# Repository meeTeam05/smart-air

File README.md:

# smart-air

> `smart-air` is an ESP32-S3 indoor air quality monitor and smart home controller. It combines ESP-IDF firmware, a Fastify + EMQX + TimescaleDB server stack, and a Flutter mobile app to solve device onboarding, telemetry ingestion, remote control, and live state sync in one system.

## Introduction

Devices provision over BLE, publish telemetry/shadow over MQTT, and serve the app through a Cloudflare-fronted Fastify API. See **Features** below for the full breakdown. See the **Hardware** section for the board, sensors, and enclosure.

## Features

- **Firmware** (ESP-IDF v5.4.2): BLE provisioning, Wi-Fi, MQTT over TLS/WSS, HTTPS OTA with rollback/validation, SHT3x (temperature/humidity), GM702B (CO) and GM102B (NO₂) gas sensors, DS3231 RTC with SNTP sync, LVGL on ILI9225 display, 3 relay channels (Fan/Lamp/Filter) with NVS persistence, WS2812 status LED, buzzer, and factory-reset button.
- **Server**: Fastify API with PostgreSQL/TimescaleDB, Redis, and EMQX in Docker Compose; Nginx + Cloudflare Tunnel for public ingress; per-device MQTT credentials provisioned through the API; OTA artifact hosting.
- **Realtime**: Live device status, shadow, telemetry, OTA progress, and command updates over Server-Sent Events; REST remains canonical for snapshots, history, replay, and command authorization.
- **App** (Flutter + Riverpod): JWT auth with refresh-token rotation in secure storage, 5-step BLE provisioning, multi-home/room management with member invites, device dashboard with relay and device-mode controls, real-time sparkline charts, command history, sensor calibration wizard, OTA screen, in-app notifications, and adaptive light/dark theme.

## Hardware

### Schematic

### PCB Layout

### 3D Model

### Assembly

## Firmware

### Config and build

### Runtime

## App

### Demo

## Contributing

- For structural work, also read `docs/ARCHITECTURE.md`, `docs/MQTT_PROTOCOL.md`, and `docs/API_REFERENCE.md`.
- Keep changes narrow, update matching docs when contracts change, and run the narrowest verification for the area you touched.

## License

MIT. See [LICENSE.md](LICENSE.md).

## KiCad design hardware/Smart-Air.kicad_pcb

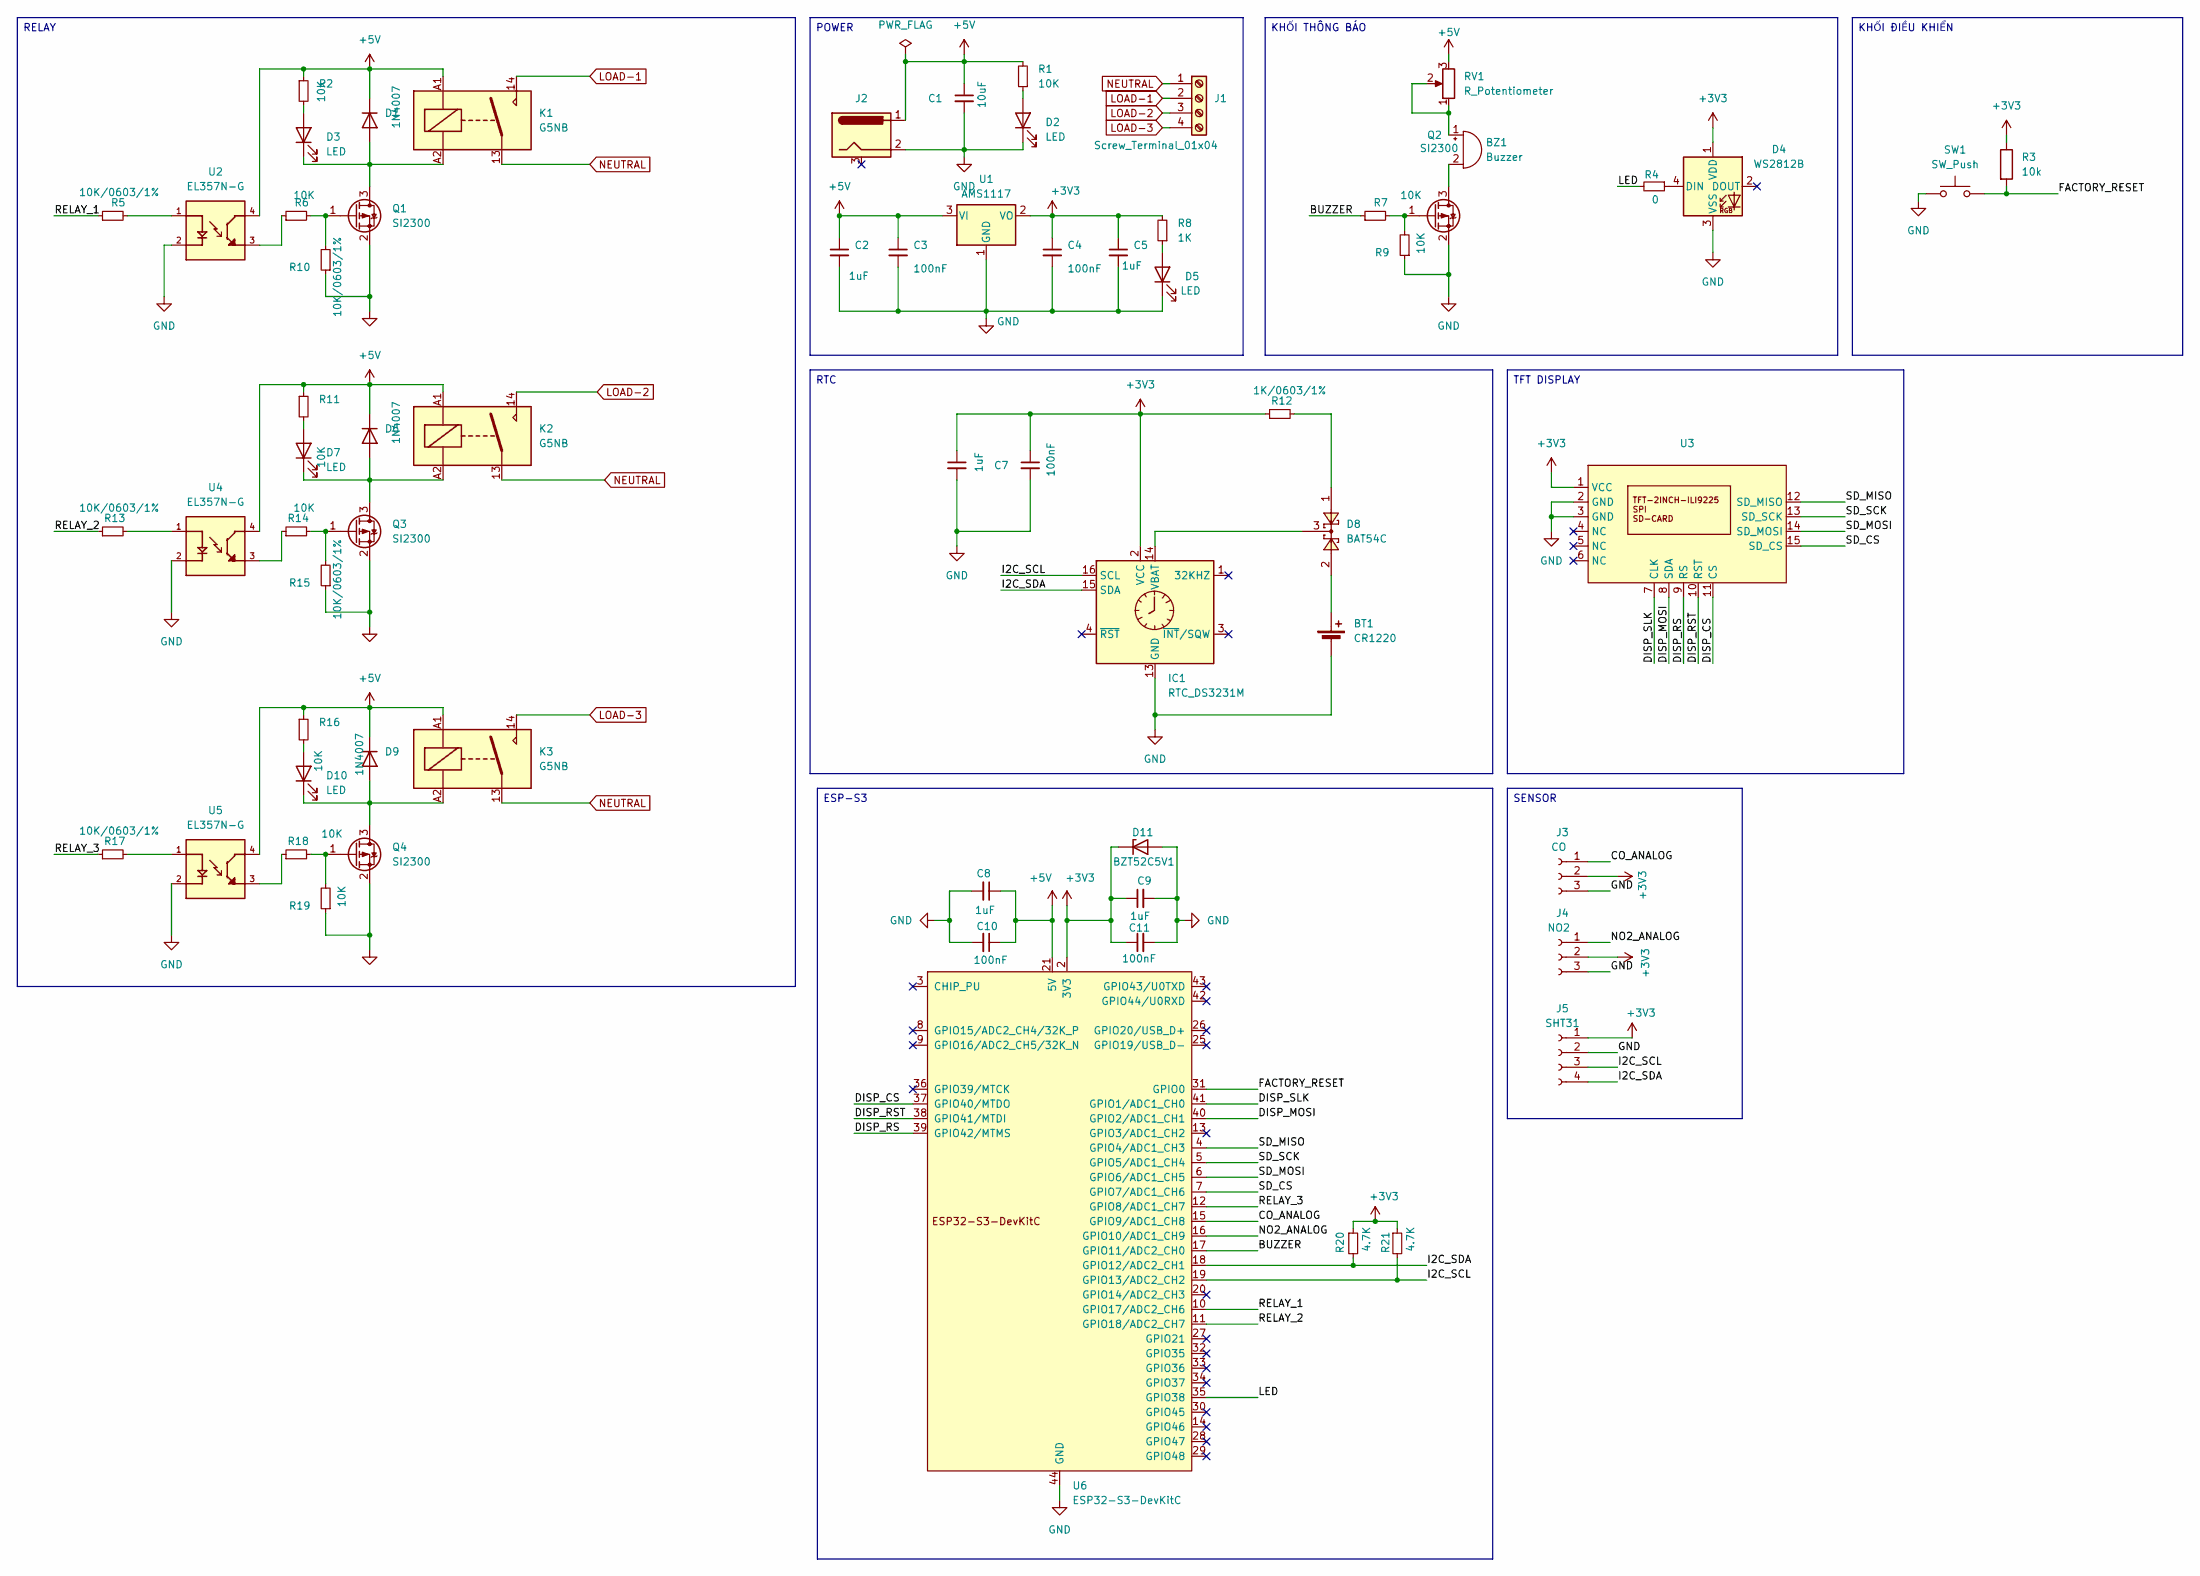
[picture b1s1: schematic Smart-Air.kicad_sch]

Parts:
BT1: CR1220; BatteryHolder-SMD-CR1220
BZ1: Buzzer; Buzzer-THT-12x9.5_RM7.6
C1: 10uF; C_0603
C2, C5, C6, C8, C9: 1uF; C_0603
C3, C4, C7, C10, C11: 100nF; C_0603
D1, D6, D9: 1N4007; D_SOD-123F
D2, D3, D5, D7, D10: LED; LED_0603_1608Metric
D4: WS2812B; LED_WS2812B_PLCC4_5.0x5.0mm_P3.2mm
D8: BAT54C; SOT23-3
D11: BZT52C5V1; D_SOD-123F
IC1: RTC_DS3231M; SOIC-16W_7.5x10.3mm_P1.27mm
J1: Screw_Terminal_01x04; HB9500-4P
J2: Conn_Jack-DC; BarrelJackDC-Horz-THT-5mm
J3: CO; PinSocket_1x03_P2.54mm_Vertical
J4: NO2; PinSocket_1x03_P2.54mm_Vertical
J5: SHT31; PinSocket_1x04_P2.54mm_Vertical
K1, K2, K3: G5NB; Relay_SPST_Omron_G5NB
Q1, Q2, Q3, Q4: SI2300; SOT-23
R1, R2, R6, R7, R9, R11, R14, R16, R18, R19: 10K; R_0603
R3: 10k; R_0603
R4: 0; R_0603
R5, R10, R13, R15, R17: 10K/0603/1%; R_0603
R8: 1K; R_0603
R12: 1K/0603/1%; R_0603
R20, R21: 4.7K; R_0603
RV1: R_Potentiometer; Potentiometer_Bourns_3266Y_Vertical
SW1: SW_Push; SW_PUSH_6mm
U1: AMS1117; SOT233
U2, U4, U5: EL357N-G; OPTO_EL357N-G; PARTREV 6
U3: TFT-ILI9225
U6: ESP32-S3-DevKitC

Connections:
+3V3: C4.1, C5.1, C6.1, C7.1, C9.1, C11.1, D4.1 (VDD), D11.1 (K), IC1.2 (VCC), J3.2, J4.2, J5.1, R3.1, R8.2, R12.1, R20.1, R21.1, U1.2 (VO), U3.1 (VCC), U6.1 (3V3), U6.2 (3V3)
+5V: C1.1, C2.1, C3.1, C8.1, C10.1, D1.1 (K), D6.1 (K), D9.1 (K), J2.1, K1.A1, K2.A1, K3.A1, R1.2, R2.1, R11.1, R16.1, RV1.3, U1.3 (VI), U2.4, U4.4, U5.4, U6.21 (5V)
/BUZZER: R7.1, U6.17 (GPIO11/ADC2_CH0)
/CO_ANALOG: J3.1, U6.15 (GPIO9/ADC1_CH8)
/DISP_CS: U3.11 (CS), U6.37 (GPIO40/MTDO)
/DISP_MOSI: U3.8 (SDA), U6.40 (GPIO2/ADC1_CH1)
/DISP_RS: U3.9 (RS), U6.39 (GPIO42/MTMS)
/DISP_RST: U3.10 (RST), U6.38 (GPIO41/MTDI)
/DISP_SLK: U3.7 (CLK), U6.41 (GPIO1/ADC1_CH0)
/FACTORY_RESET: R3.2, SW1.2, U6.31 (GPIO0)
/I2C_SCL: IC1.16 (SCL), J5.3, R21.2, U6.19 (GPIO13/ADC2_CH2)
/I2C_SDA: IC1.15 (SDA), J5.4, R20.2, U6.18 (GPIO12/ADC2_CH1)
/LED: R4.2, U6.35 (GPIO38)
/NO2_ANALOG: J4.1, U6.16 (GPIO10/ADC1_CH9)
/RELAY_1: R5.1, U6.10 (GPIO17/ADC2_CH6)
/RELAY_2: R13.1, U6.11 (GPIO18/ADC2_CH7)
/RELAY_3: R17.1, U6.12 (GPIO8/ADC1_CH7)
/SD_CS: U3.15 (SD_CS), U6.7 (GPIO7/ADC1_CH6)
/SD_MISO: U3.12 (SD_MISO), U6.4 (GPIO4/ADC1_CH3)
/SD_MOSI: U3.14 (SD_MOSI), U6.6 (GPIO6/ADC1_CH5)
/SD_SCK: U3.13 (SD_SCK), U6.5 (GPIO5/ADC1_CH4)
GND: BT1.2 (-), C1.2, C2.2, C3.2, C4.2, C5.2, C6.2, C7.2, C8.2, C9.2, C10.2, C11.2, D2.1 (K), D4.3 (VSS), D5.1 (K), D11.2 (A), IC1.5 (GND), IC1.6 (GND), IC1.7 (GND), IC1.8 (GND), IC1.9 (GND), IC1.10 (GND), IC1.11 (GND), IC1.12 (GND), IC1.13 (GND), J2.2, J3.3, J4.3, J5.2, Q1.2 (S), Q2.2 (S), Q3.2 (S), Q4.2 (S), R9.1, R10.1, R15.1, R19.1, SW1.1, U1.1 (GND), U2.2, U3.2 (GND), U3.3 (GND), U4.2, U5.2, U6.22 (GND), U6.23 (GND), U6.24 (GND), U6.44 (GND)
LOAD-1: J1.2, K1.14
LOAD-2: J1.3, K2.14
LOAD-3: J1.4, K3.14
NEUTRAL: J1.1, K1.13, K2.13, K3.13
unnamed: BT1.1 (+), D8.2
unnamed: BZ1.1 (+), RV1.1, RV1.2
unnamed: BZ1.2 (-), Q2.3 (D)
unnamed: D1.2 (A), D3.1 (K), K1.A2, Q1.3 (D)
unnamed: D2.2 (A), R1.1
unnamed: D3.2 (A), R2.2
unnamed: D4.4 (DIN), R4.1
unnamed: D5.2 (A), R8.1
unnamed: D6.2 (A), D7.1 (K), K2.A2, Q3.3 (D)
unnamed: D7.2 (A), R11.2
unnamed: D8.1, R12.2
unnamed: D10.2 (A), R16.2
unnamed: D9.2 (A), D10.1 (K), K3.A2, Q4.3 (D)
unnamed: D8.3, IC1.14 (VBAT)
unnamed: Q1.1 (G), R6.2, R10.2
unnamed: Q2.1 (G), R7.2, R9.2
unnamed: Q3.1 (G), R14.2, R15.2
unnamed: Q4.1 (G), R18.2, R19.2
unnamed: R5.2, U2.1
unnamed: R6.1, U2.3
unnamed: R13.2, U4.1
unnamed: R14.1, U4.3
unnamed: R17.2, U5.1
unnamed: R18.1, U5.3

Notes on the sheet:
RELAY
SENSOR
TFT DISPLAY
ESP-S3
RTC
POWER
KHỐI THÔNG BÁO
KHỐI ĐIỀU KHIỂN

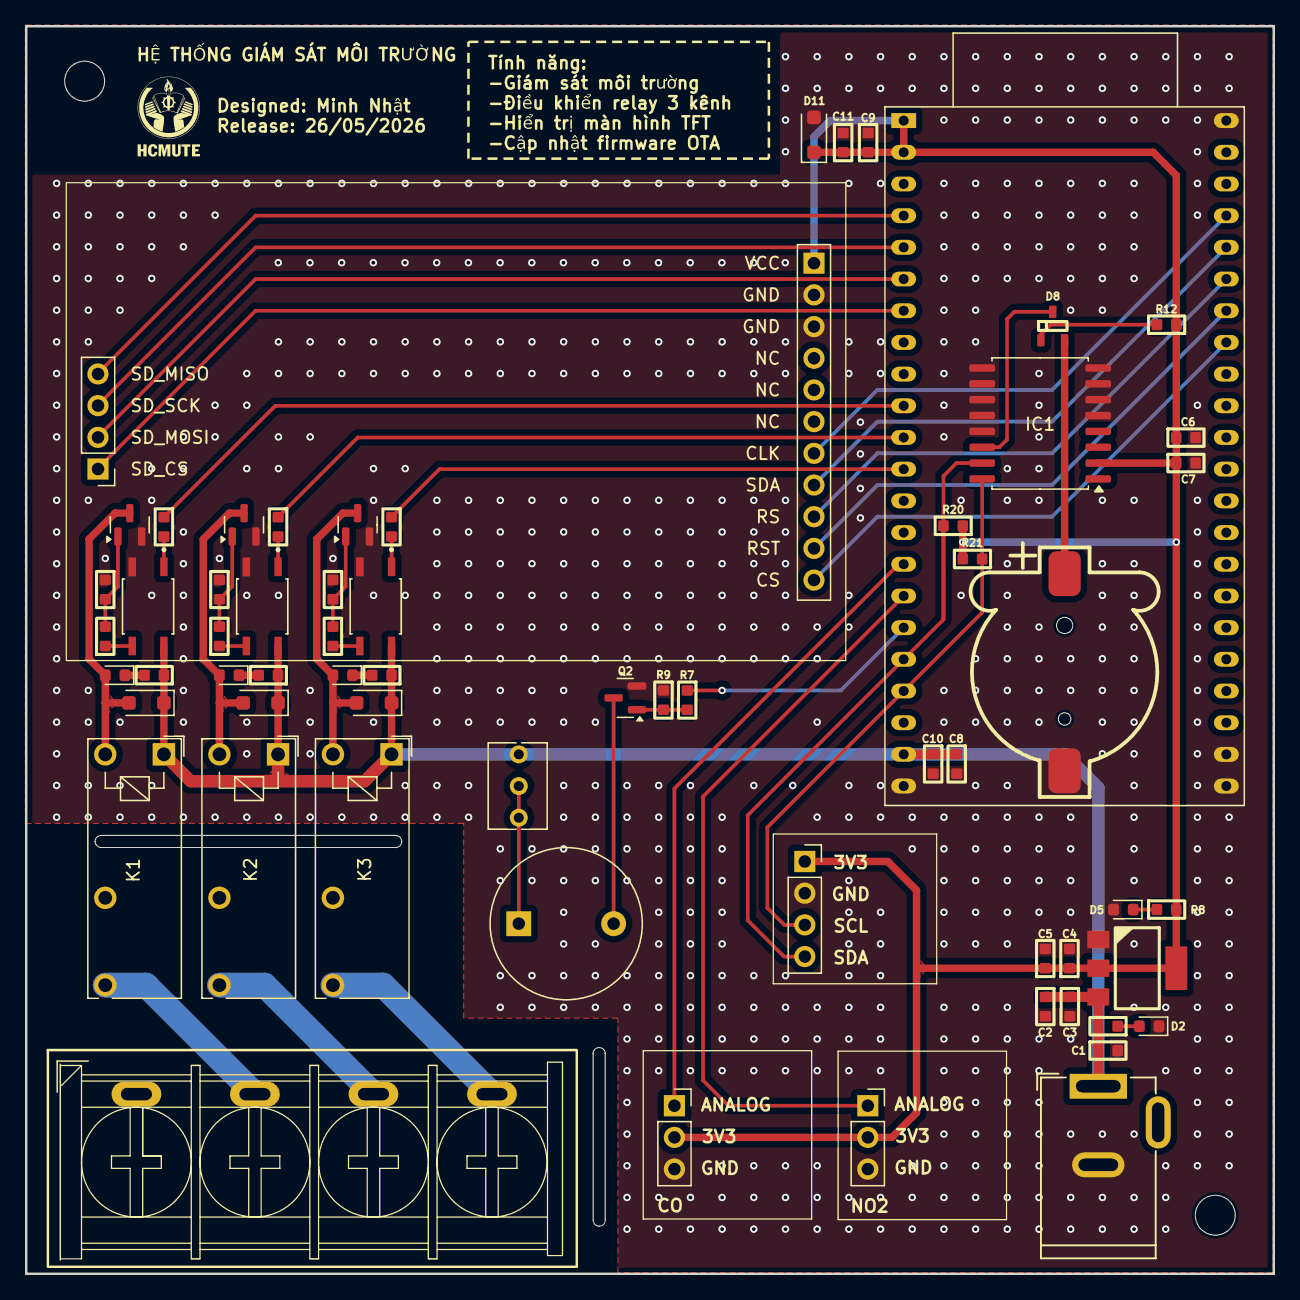
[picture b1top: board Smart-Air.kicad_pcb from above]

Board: 2 copper layers, 100.0 x 100.0 mm, 62 parts (0 on the bottom side), 47 nets.

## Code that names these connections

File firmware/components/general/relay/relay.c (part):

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#define RELAY_BEEP_MS_ALL_OFF 100

#define RELAY_NVS_NAMESPACE "device"
#define RELAY_KEY_1         "relay_1"
#define RELAY_KEY_2         "relay_2"
#define RELAY_KEY_3         "relay_3"

static const char *TAG = "relay";

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
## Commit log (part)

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2026-03-13 docs: add .gitignore, LICENSE, and README documents
2026-03-18 feat: add buzzer driver implementation files
2026-03-18 feat: add LED driver implementation files
2026-03-18 feat: add webserver component files including CMake, headers, HTML, CSS, JS, and source
2026-03-18 feat: add DS3231 RTC driver implementation files and headers
2026-03-18 feat: add SPI bus driver implementation files and headers
2026-03-18 feat: add XPT2046 touch controller driver implementation files and headers
2026-03-18 feat: add initial firmware structure with CMakeLists, Kconfig, linker script, main file, and partitions
2026-03-18 feat: add .clang-format file for ESP-IDF / ESP32 firmware style
2026-03-18 docs: create CHANGELOG.md to document project updates
2026-03-18 docs: add foundational documentation files for project structure and guidelines
2026-04-13 fix(emqx): add required node block lost when mounting custom emqx.conf
2026-04-13 fix(emqx): add dashboard HTTP listener — required explicit in EMQX 6.x
2026-04-14 docs(architecture): expand system architecture and protocol docs
2026-04-14 feat(hardware): add KiCad project and reusable hardware libraries
2026-04-14 feat(config): add CA certificate for secure communication
2026-04-14 feat(mqtt): migrate MQTT client to sa_mqtt component with TLS support
2026-04-14 feat(ota): implement HTTPS OTA firmware update with progress reporting and rollback
2026-04-14 feat(routes): add authentication, device commands, telemetry, and health check endpoints
2026-04-14 feat(emqx): add EMQX API integration for device user management feat(shadow): implement device shadow management with caching
2026-04-14 feat(nginx): add HTTPS server configuration for OTA firmware and health check
2026-04-14 feat(docker): update docker-compose.yml for service configurations and volume mappings
2026-04-14 refactor(docker-compose, nginx): clean up comments and formatting for clarity
2026-04-14 feat(emqx): enable Plain MQTT listener on port 1883 and configure binding
2026-04-14 feat(db): change device ID type from UUID to TEXT and update related constraints
2026-04-14 feat(scripts): add various database interaction scripts for device management
2026-04-14 feat(core): implement API client, authentication interceptor, secure storage, and routing
2026-04-14 feat(security): add network security configuration to allow cleartext HTTP for local IPs
2026-04-14 feat(device): add Device and DeviceShadow models with JSON serialization
2026-04-14 feat(telemetry): add TelemetryPoint model with JSON serialization support
2026-04-14 feat(auth): implement AuthNotifier with login, register, and logout functionality
2026-04-14 feat(homes): implement HomesNotifier and RoomsNotifier for home and room management
2026-04-14 feat(homes): add CreateHomeScreen, HomeDetailScreen, and HomesScreen for home management
2026-04-14 feat(provision): add BleScanScreen and WifiSetupScreen for device provisioning
2026-04-14 feat(ble): update GATT UUIDs and enhance BLE service for provisioning
2026-04-14 feat(main): refactor SmartAirApp to use ConsumerStatefulWidget and update theme change handling
2026-04-14 feat(storage): integrate flutter_secure_storage plugin across platforms
2026-04-14 feat(devices): add provisioning poll endpoint to check device online status
2026-04-14 feat(ble_prov): update GATT characteristics to allow write responses for SSID and Password
2026-04-14 feat(factory_reset): implement factory reset functionality with GPIO monitoring and reset sequence
2026-04-14 refactor(mqtt): simplify status update logic and improve provisioning announcement handling
2026-04-15 feat(router): add route for creating a new home
2026-04-15 refactor(wifi_setup): streamline provisioning logic and remove unused components
2026-04-15 feat(sensor_task): include device timestamp in shadow report; increase shadow buffer size
2026-04-15 feat(ble_prov): include device MAC address in provisioning JSON response
2026-04-15 fix(telemetry): correct aliasing in SQL queries for time bucket and payload extraction
2026-04-15 feat(theme): update color palette and enhance theme data for dark and light modes
2026-04-15 fix(gitignore): add firmware/managed_components to .gitignore
2026-05-11 chore(app): point default API to public domain
2026-05-11 docs(repo): refresh API and protocol references
2026-05-11 test: add 390dp counterpart verification suite
    - Create counterpart matrix mapping all 20 mockup screens to Flutter implementations
    - Add deterministic 390dp viewport tests for all screens
    - Coverage: 100% (Auth, Home, Dashboard, Charts, Settings, BLE, Tabs)
    - All 20 tests pass with zero exceptions
    - Verification strategy: widget presence + exception guards (no browser dependency)
    Completes DoD: 'Every screen in tmp/app/ has Flutter counterpart at 390dp width'
2026-05-13 server: add api packaging and db migrations
2026-05-13 server: harden device lifecycle and mqtt runtime
2026-05-13 remove: remove sisyphus opencode
2026-05-13 firmware: reorganize core and general components
2026-05-13 firmware: replace shared defaults with explicit demo preset
2026-05-15 chore(server): align mqtt proxy and local tls config
2026-05-15 docs: refresh architecture and protocol references
2026-05-15 feat(app): consume realtime API stream in device UI
2026-05-15 docs(repo): refresh architecture and repository docs
2026-05-18 refactor(firmware): align runtime config with SA defaults
    Wire runtime naming and common ports/pins through SA_* config macros.\nSet ESP32-S3 target defaults and keep tracked sdkconfig defaults aligned with the selected hardware profile.
2026-05-18 firmware: move calibration off MQTT callback
2026-05-18 firmware: retry telemetry after publish failures
2026-05-18 firmware: clean up adc bus init failures
2026-05-18 firmware: harden co calibration quality
2026-05-18 firmware: keep ds3231 timestamps in utc
2026-05-18 firmware: unregister wifi event handlers
2026-05-18 firmware: split sysload boot stages
2026-05-18 firmware: clarify public header docs
2026-05-18 firmware: validate ds3231 calendar dates
2026-05-18 firmware: fail fast on mqtt command registration errors
2026-05-18 firmware: guard ota task startup
2026-05-18 firmware: name legacy device id nvs key
2026-05-19 fix(codex): minimal coding agents
2026-05-19 docs: add datasheets for sensor
2026-05-19 docs: add operational runbook for smart-air server stack
2026-05-19 refactor: sync coding style
2026-05-19 fix(server): reject wildcard cors origins in production
2026-05-19 fix(server): avoid refresh self-revocation race
2026-05-19 fix(server): dedupe qos1 telemetry redelivery
2026-05-19 fix(server): dedupe replayable realtime events
2026-05-19 fix(server): avoid advisory lock hash collisions
2026-05-19 fix(server): add api retention cleanup job
2026-05-19 perf(server): reuse mqtt payload byte lengths
2026-05-19 refactor(server): share email validation helpers
2026-05-19 fix(server): run command timeout sweep on startup
2026-05-19 fix(server): add nginx api rate limits
2026-05-19 fix(server): add hsts headers
2026-05-19 fix(server): use fastify logger for emqx cleanup failures
2026-05-19 style(server): rename auth rate limit config
2026-05-19 fix(codex): update skill for agents
2026-05-21 fix(server): enable nginx keepalive for api proxy
2026-05-21 docs(server): document telemetry range limits
2026-05-21 docs(server): document device mode endpoint
2026-05-21 docs(server): document device list status fields
2026-05-21 test(server): cover device list pagination order
2026-05-21 fix(server): tighten health and mqtt readiness
2026-05-21 fix(server): harden command dispatch timing and bounds
2026-05-21 fix(server): protect logs and realtime capacity
2026-05-21 fix(server): pin fast-uri dependency
2026-05-22 fix(firmware): preserve wifi credentials on connect failure
2026-05-22 fix(firmware): guard task publishes during factory reset
2026-05-22 fix(firmware): serialize wifi reconnect counter
2026-05-22 fix(firmware): guard gas calibration state
2026-05-22 fix(firmware): preserve mode state on publish failure
2026-05-22 fix(firmware): start local api before sntp sync
2026-05-22 fix(firmware): serialize buzzer access
2026-05-22 fix(firmware): validate sensor readings before publish
2026-05-22 fix(firmware): use log interpolation for no2 curve
2026-05-22 fix(firmware): retry failed mqtt subscriptions
2026-05-22 fix(firmware): use correct sensor task critical API
2026-05-22 fix(firmware): stop timed out wifi connects
2026-05-23 fix(firmware): update NO2 concentration curve for improved accuracy
2026-05-24 fix(app): guard wifi setup status updates after async steps
2026-05-24 fix(server): remove duplicate shadow sync on reconnect
2026-05-24 fix(firmware): dedupe repeated mqtt commands
2026-05-24 fix(app): validate endpoint env values at startup
2026-05-24 fix(app): guard malformed realtime timestamps
2026-05-24 fix(app): clear corrupt stored user session
2026-05-24 fix(app): validate home service response bodies
2026-05-24 fix(server): clamp future shadow report ts
2026-05-24 fix(server): persist firmware version from status
2026-05-24 fix(app): cancel realtime reconnect backoff
2026-05-24 docs(firmware): align mqtt status payload examples
2026-05-24 fix(app): guard malformed provisioning routes
2026-05-24 fix(firmware): clean up wifi init failure path
2026-05-24 fix(firmware): report provisioning recv failures
2026-05-24 chore(firmware): document BLE provisioning trust model
2026-05-24 fix(firmware): tolerate wifi teardown edge states
2026-05-24 fix(firmware): clean up failed calibration task start
2026-05-24 fix(httpd): handle errors during URI handler registration
2026-05-24 fix(app): preserve distinct same-second telemetry points
2026-05-24 docs(server): align provisioning announce timeout
2026-05-24 fix(firmware): clarify empty shadow delta log
2026-05-24 fix(server): cast telemetry timestamps before persistence
2026-05-24 refactor(app): remove chart entry from device dashboard
2026-05-24 fix(app): prevent sensor tile overflow on large values
2026-05-25 docs: add server architecture document
2026-05-25 docs: refresh system architecture document
2026-05-25 feat(server): add notifications feed
2026-05-25 docs: update MQTT protocol documentation for clarity and structure
2026-05-25 feat(scripts): add telemetry csv export
2026-05-25 fix(server): align ota hash with esp image digest
2026-05-25 feat(data): add csv for mlai
2026-05-26 fix(i2c): update SDA and SCL pin definitions for I2C scanner
2026-06-04 fix(app): refresh devices after realtime reset and app resume
2026-06-04 feat(firmware): render full display dashboard
2026-06-04 chore(tooling): refresh repo agent metadata
2026-06-04 chore(tooling): refresh gitnexus metadata counts
2026-06-04 fix(firmware): apply local timezone to display clock
2026-06-04 feat(data): refresh telemetry flat samples
2026-06-05 feat(app): improve BLE scan preflight handling
2026-06-05 chore(server): remove Grafana service
2026-06-05 feat(calibration): update calibration timeout and add test for confirmation duration
2026-06-05 feat(config): add WebSocket buffer size and dynamic buffer configuration
2026-06-05 feat(docs): add app demo GIFs to README
2026-06-05 feat(docs): enhance README with detailed features and app capabilities
2026-06-06 chore: remove ai assistant files
2026-06-25 feat(ai-service): random forest network
2026-06-25 feat(ai-service): trained model
2026-06-25 feat(ai-service): add thread-safety, token cache management, and error handling
2026-06-25 remove: remove AI asssistant
2026-06-26 fix(ble): enable lowLatency scan mode for faster device discovery
2026-06-26 refactor(ai-service): replace JWT+HTTP with MQTT direct and DB direct
    - Remove JWT login flow from AI service; service no longer needs
    AI_EMAIL or AI_PASSWORD credentials
    - Read auto_mode directly from devices table via psycopg2 instead of
    polling GET /api/devices through the user-facing API
    - Publish relay commands directly to device/{id}/command via MQTT
    instead of POST /api/devices/{id}/relay/{channel}; adds "type":

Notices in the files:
firmware/components/general/relay/relay.c:
Copyright (C) 2026 MinhNhat & BaoViet
